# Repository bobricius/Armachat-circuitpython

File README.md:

# Armachat-circuitpython
New Armachat based on Raspberry Pi PICO an Circuitpython code

**Software working features:**

- send message with header and store to memory
- receive message and parse header, store to memory
- display message memory with message details like SNR and RSSI
- count messages in memory by type
- display some hardware details like free memory and power supply voltage, it is good for future battery operation
- Terminal display with messages from background systems
- AES256 encryption
- message confirmation and status change in memory
- boot safe mode

**TODO:**

- Need much better LoRa library with, CAD, status detection, and INTERRUPT !!!
- contact list
- ~~setup and save configuration~~
- save memory to flash

##Fixes in this repository

- Much more stable
- Formatting changes in all three files. I'm using the Mu editor, <a href="https://codewith.mu/">https://codewith.mu/</a>, that has Check and Tidy functions to help standardize formatting. The formatting changes are from using those functions in the Mu editor.
- Configuration values that  are changed may be saved to a config.txt file if the file-system is writable. 

**boot.py**

- Pull model information from config.py to obtain the model and keyboard setup information.
- Used the adafruit_matrixkeypad to scan the keyboard.
- Display prompts based on the Armachat model
- Added a progress bar to show remaining time to make a selection for safe and write modes.

**code.py**

- Added a function named screenSafeText, which removed characters from a string that is a non-printable character. There were some random errors due to received messages having non-printable characters. When the messages were displayed, there would be no font in the font file for them, which would cause the code to crash.
- Added a 0.1 second delay when checking for a key press. I was experiencing skipping screens as the left or right button (bsp, ent) was read twice or more on one key press. This is not a perfect solution but the results in a better user experience.
- Added try/catch blocks around attempts to read or write files. I would have rather used file exists for reads but it appears that CircuitPython's file library does not have an exists function. The use of try/catch blocks appears to be the preferred method to check for a file's existence.
- Created the function radioInit to allow changing of the LoRa radio on the fly.
- Added the CPU Temperature from Kayto's code
- Added the Ping function from Kayto's code
- Allow changing the frequency on the fly
- Allow changing the power on the fly
- Matched LoRa profiles to Meshtastic's profiles

**config.py**

Now reading and writing to config.txt file to keep settings between reboots

Notes:

- If a new property is added to config.py, it will be written to config.txt if it is one of the types included in config_includeTypes list.
- A property may be excluded by placing it in the config_excludeNames list.

Limitations

- To save configuration changes, the file-system needs to be changed to writable on boot by pressing the ALT key.
- If the config.txt file is edited by hand comments are allowed but the whole line must be a comment. Inline comments are not allowed.
- If a hex, binary. or octal value is in the config.txt file, it will be changed to decimal if the configuration file is saved.
- Currently only str, int, and float types are supported.

BTW: Save memory to flash does work if you change the file system to write mode by pressing the ALT key when booting and pressing the S key when viewing messages.

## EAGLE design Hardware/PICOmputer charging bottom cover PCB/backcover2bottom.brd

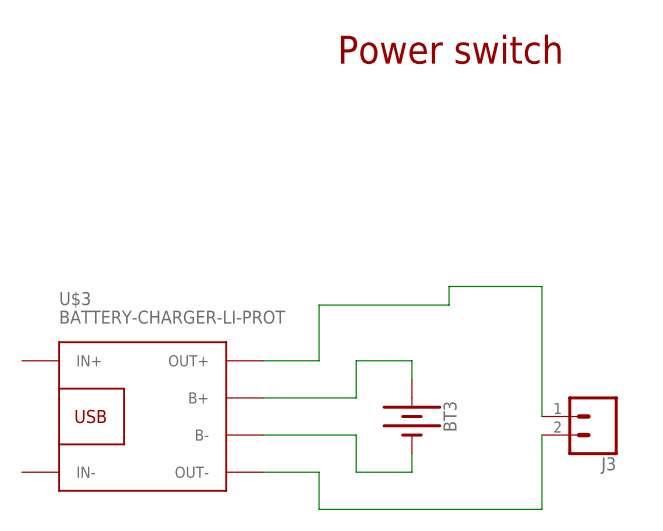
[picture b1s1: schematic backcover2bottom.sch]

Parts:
BT3: BATTERY; 18650_HOLDER_SINGLE_THROUGH-HOLE
J3: CONN_02PTH3; 1X02_LONGPADS
U$3: BATTERY-CHARGER-LI-PROT

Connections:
unnamed: BT3.CON(+) (+), U$3.B+
unnamed: BT3.CON(-) (-), U$3.B-
unnamed: J3.2, U$3.OUT-
unnamed: J3.1, U$3.OUT+

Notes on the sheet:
Power switch

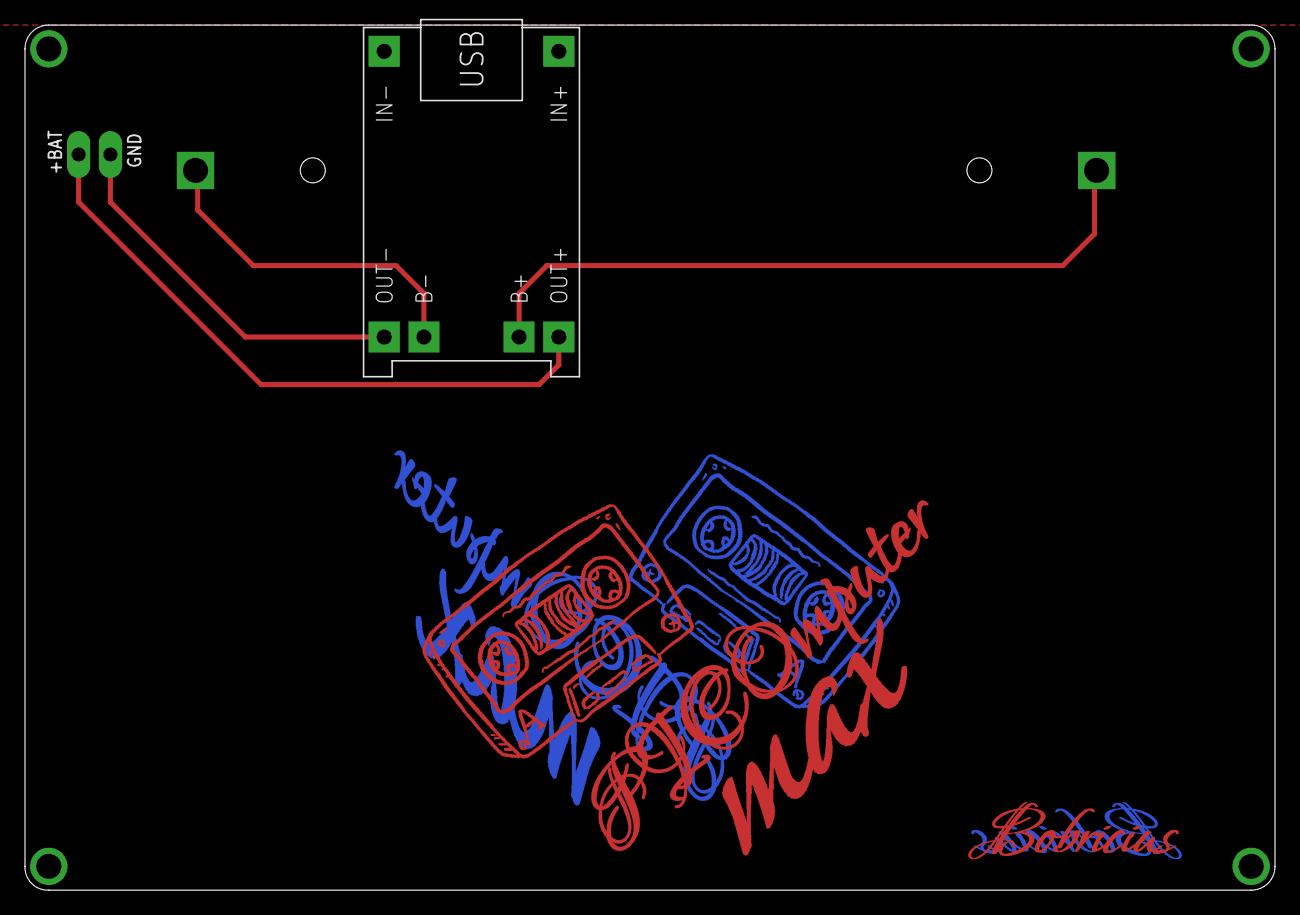
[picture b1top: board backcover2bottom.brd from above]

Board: 2 copper layers, 100.0 x 69.2 mm, 3 parts (1 on the bottom side), 4 nets.

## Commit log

2021-11-21 Add files via upload
    First init
2021-11-21 Safe mode, drive rename
    +Safe mode, If you press on boot ESC, user program not started
    +drive reamed to ARMACHAT
    +USB detection ... for future disable disk write protection ...
2021-11-24 Delivery confirmation
2021-11-27 GPS, I2C test
2022-01-23 COMPACT update
2022-03-02 Start of Documentation - BOM - Datasheets
2022-03-02 Added MarkDown version of BOM
2022-03-07 Some code fixes
2022-03-07 Fixed various Mu editor code formatting issues and checks
2022-03-08 Commented unused libraries
2022-03-08 Fixed a bugs with displaying messages after sending a message
2022-03-08 UI changes
    -default is graphics font +enabled extra line for UI hints
    -font are converted to PCF ... faster loading
    -prepared for radio profiles
2022-03-08 Updated README.md with some notes regarding this repository
2022-03-09 Added new code by bobricius
    - UI changes
2022-03-09 Allow changing and applying radio profiles - Not certain if there will be issues with memory if done multiple times. I believe the GC will clean up the memory. - I had one crash. Not certain what the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
2022-03-09 UI design changes
    Font faster loading
    UI design changes
2022-03-09 codingRate was set to 8 when it should be 2
2022-03-09 Nope, codingRate was originally 8
2022-03-10 The line "if packet[16] == 33:" had been giving me problems and I mistook it as "if header[16] == 33:", which would result in an error as there are only 16 elements in that array. I just realized tha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
2022-03-10 - boot.py pulls from config.py for model and keys - boot.py supports Max and Compact models. (Only tested on Compact but expected to work fine on Max version) - boot.py has a progress bar to show tim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
2022-03-12 Reversed the countdown progress bar
2022-03-12 It is possible that I missed something, but I believe this complete list of changes.
    - Formatting changes in all three files. I'm using the Mu editor, https://codewith.mu/, that has Check and Tidy functions to help standardize formatting. The formatting changes are from using those f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
    **boot.py**
    - Pull model information from config.py to obtain the model and keyboard setup information.
    - Used the adafruit_matrixkeypad to scan the keyboard.
    - Display prompts based on the Armachat model
    - Added a progress bar to show remaining time to make a selection for safe and write modes.
2022-03-12 Noticed that not all of the modemPreset values were allowing messages to be sent. Validated settings against the datasheet from Hoperf Electronic (RF96_97_98.pdf pages 106 & 107 of 121) and found tha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
    Validated that the modified 6 modemPreset values worked. Messages from each modemPreset was received on another unit with the same modemPreset value.
2022-03-12 - Added back lost change to show progress timeout bar starting full and emptying as time runs down - Modified config.py comment for the loraProfile settings to match new values that match Meshtastic 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
2022-03-13 - Updated README.md - Added case file - Just a shell for this version
2022-03-13 Now reading and writing to config.txt file to keep settings between reboots
    Notes:
    - If a new property is added to config.py, it will be written to config.txt if it is one of the types included in config_includeTypes list.
    - A property may be excluded by placing it in the config_excludeNames list.
    Limitations
    - To save configuration changes, the file-system needs to be changed to writable on boot by pressing the ALT key.
    - If the config.txt file is edited by hand comments are allowed but the whole line must be a comment. Inline comments are not allowed.
2022-03-18 DOS - Doomsday operating system
    select app to run on boot
2022-06-08 security: Updating AES mode to one that does not require a unique IV
2022-11-25 Preview new alpha software
2023-03-11 Delete New software directory
    Uploading to SOFTWARE latest code
2023-03-11 Lot of changes
    Edit destination, power and spread
    Save setting in to NVM ... destination, power and spread
    Display battery status
    Display filesystem info
    Activity on channel detection
    Receive all - ignore destination header
2023-03-13 Layout and status window
    Slightly changed the visual design
2023-03-20 PCB bottom cover for PICOmputer 1.generation
2023-08-28 redesign
2023-08-28 Add files via upload
    LIB updated
2023-08-28 Add files via upload
    Support for PICOPAD, WIO TERMINAL

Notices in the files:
parts and their libraries:
SparkFun-Connectors: Licensing: Creative Commons ShareAlike 4.0 International - https://creativecommons.org/licenses/by-sa/4.0
diy-modules: Released under the Creative Commons Attribution 4.0 International License: http://creativecommons.org/licenses/by/4.0
